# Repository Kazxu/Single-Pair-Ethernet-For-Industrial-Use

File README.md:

# Single Pair Ethernet For Industrial Use

## KICAD
KICAD PCB design files for the LTC4296-1 PSE prototype and LTC9111 PD prototype.

## SCCP 

SCCP_2 uses SPI to communicate with the LTC4296-1 prototype. 

See program print for features. 

SCCP classification between LTC4296-1 and LTC9111 can be performed as well.

## ADIN1110 - Development with STM32Cube IDE.

MCU Firmware : STM32L4xx - https://github.com/STMicroelectronics/STM32CubeL4 

LL DRIVERS : ADIN1110 Support files by Analog Devices.

TCP/IP : LWIP 2.1.2 & Callback API from LWIP. 

Serial Monitor : USART.c & USART.h, huart1.Init.BaudRate = 115200

ADC : INIT in Main.c & stm32l4xx_hal_msp.c

Client-side GUI CONCEPT PROTOTYPE - Python, Added as placeholder for showcase.

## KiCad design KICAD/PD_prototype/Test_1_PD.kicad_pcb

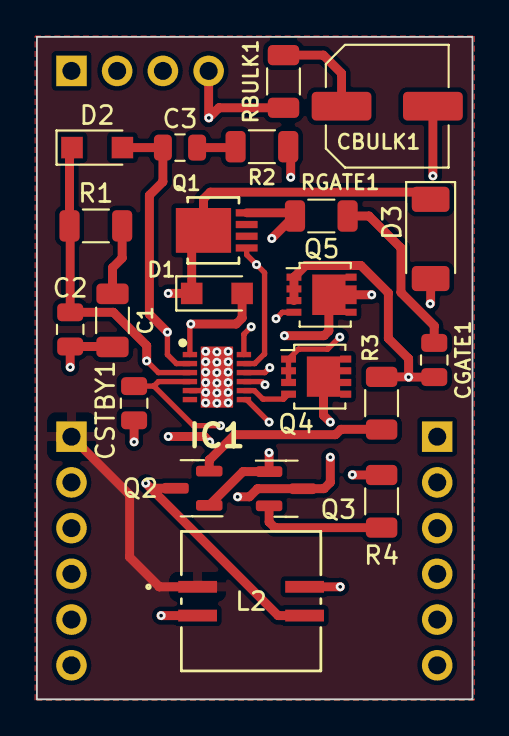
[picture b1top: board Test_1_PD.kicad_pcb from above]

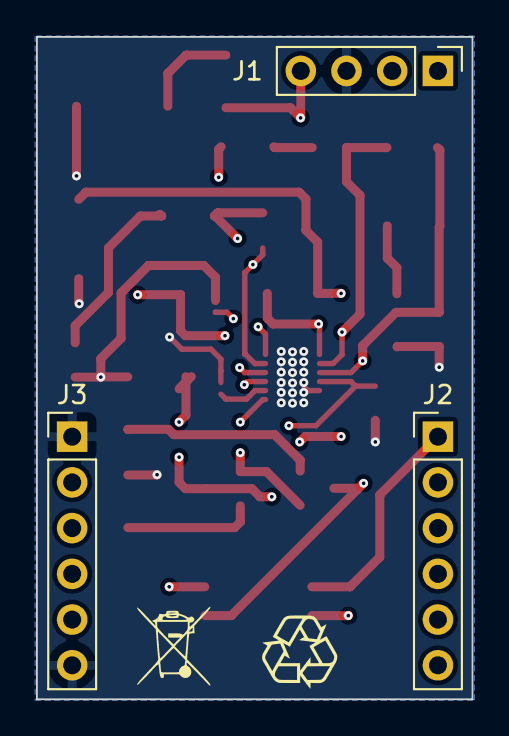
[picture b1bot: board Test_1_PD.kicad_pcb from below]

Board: 4 copper layers, 24.2 x 36.8 mm, 25 parts (3 on the bottom side), 18 nets.

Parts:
C1: 150nF; C_1206_3216Metric
C2, C3: 47nF; C_0805_2012Metric
CBULK1: 47uF; C_Elec_6.3x7.7
CGATE1: 22nF; C_0805_2012Metric
CSTBY1: 2.2uF; C_0805_2012Metric
D1, D2: PMEG10020AELR; Nexperia_CFP3_SOD-123W
D3: D_Zener; D_SOD-128
IC1: LTC9111RDE#PBF; SON50P300X400X80-13N-D
J1: Conn_01x04_Pin; PinHeader_1x04_P2.54mm_Vertical
J2, J3: Conn_01x06_Pin; PinHeader_1x06_P2.54mm_Vertical
L2: MSD7342-683MLC; MSD7342_COC
Q1: PSMN075-100MSEX; LFPAK33_SOT1210_NEX
Q2, Q3: BSS123; SOT-23
Q4, Q5: BUK9M120-100EX; LFPAK33
R1: 40, 1/4; R_1206_3216Metric
R2: 100; R_1206_3216Metric
R3, R4: 3.3, 1/4; R_1206_3216Metric
RBULK1: 3.3, 1/4; R_1206_3216Metric
RGATE1: 10k; R_1206_3216Metric

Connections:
/PODL+: J2.1, L2.1
/PODL-: J2.6, L2.4
GND: C1.2, C2.2, CBULK1.2, CGATE1.2, CSTBY1.2, D3.2 (A), IC1.5 (CLASSV), IC1.13 (GND), J1.3, J3.1, J3.6, Q4.1 (S), Q4.2 (S), Q4.3 (S), Q5.1 (S), Q5.2 (S), Q5.3 (S), R3.2, R4.2
unnamed: C1.1, R1.2
unnamed: C3.1, R2.2
unnamed: CBULK1.1, RBULK1.2
unnamed: CGATE1.1, RGATE1.2
unnamed: D1.2 (A), IC1.1 (SNS1), L2.3, Q2.3 (D), Q5.5 (D), R2.1
unnamed: C2.1, D1.1 (K), D2.1 (K), D3.1 (K), IC1.3 (IN), Q1.5 (D), R1.1
unnamed: C3.2, D2.2 (A), IC1.2 (SNS2), L2.2, Q3.3 (D), Q4.5 (D)
unnamed: CSTBY1.1, IC1.4 (STBY), IC1.10 (CLASSC)
unnamed: IC1.12 (GATE), Q1.4 (G), RGATE1.1
unnamed: IC1.9 (LGATE1), Q5.4 (G)
unnamed: IC1.8 (LGATE2), Q4.4 (G)
unnamed: IC1.11 (OUT), J1.4, Q1.1 (S), RBULK1.1
unnamed: IC1.7 (SCCP), Q2.1 (G), Q3.1 (G)
unnamed: Q2.2 (S), R3.1
unnamed: Q3.2 (S), R4.1

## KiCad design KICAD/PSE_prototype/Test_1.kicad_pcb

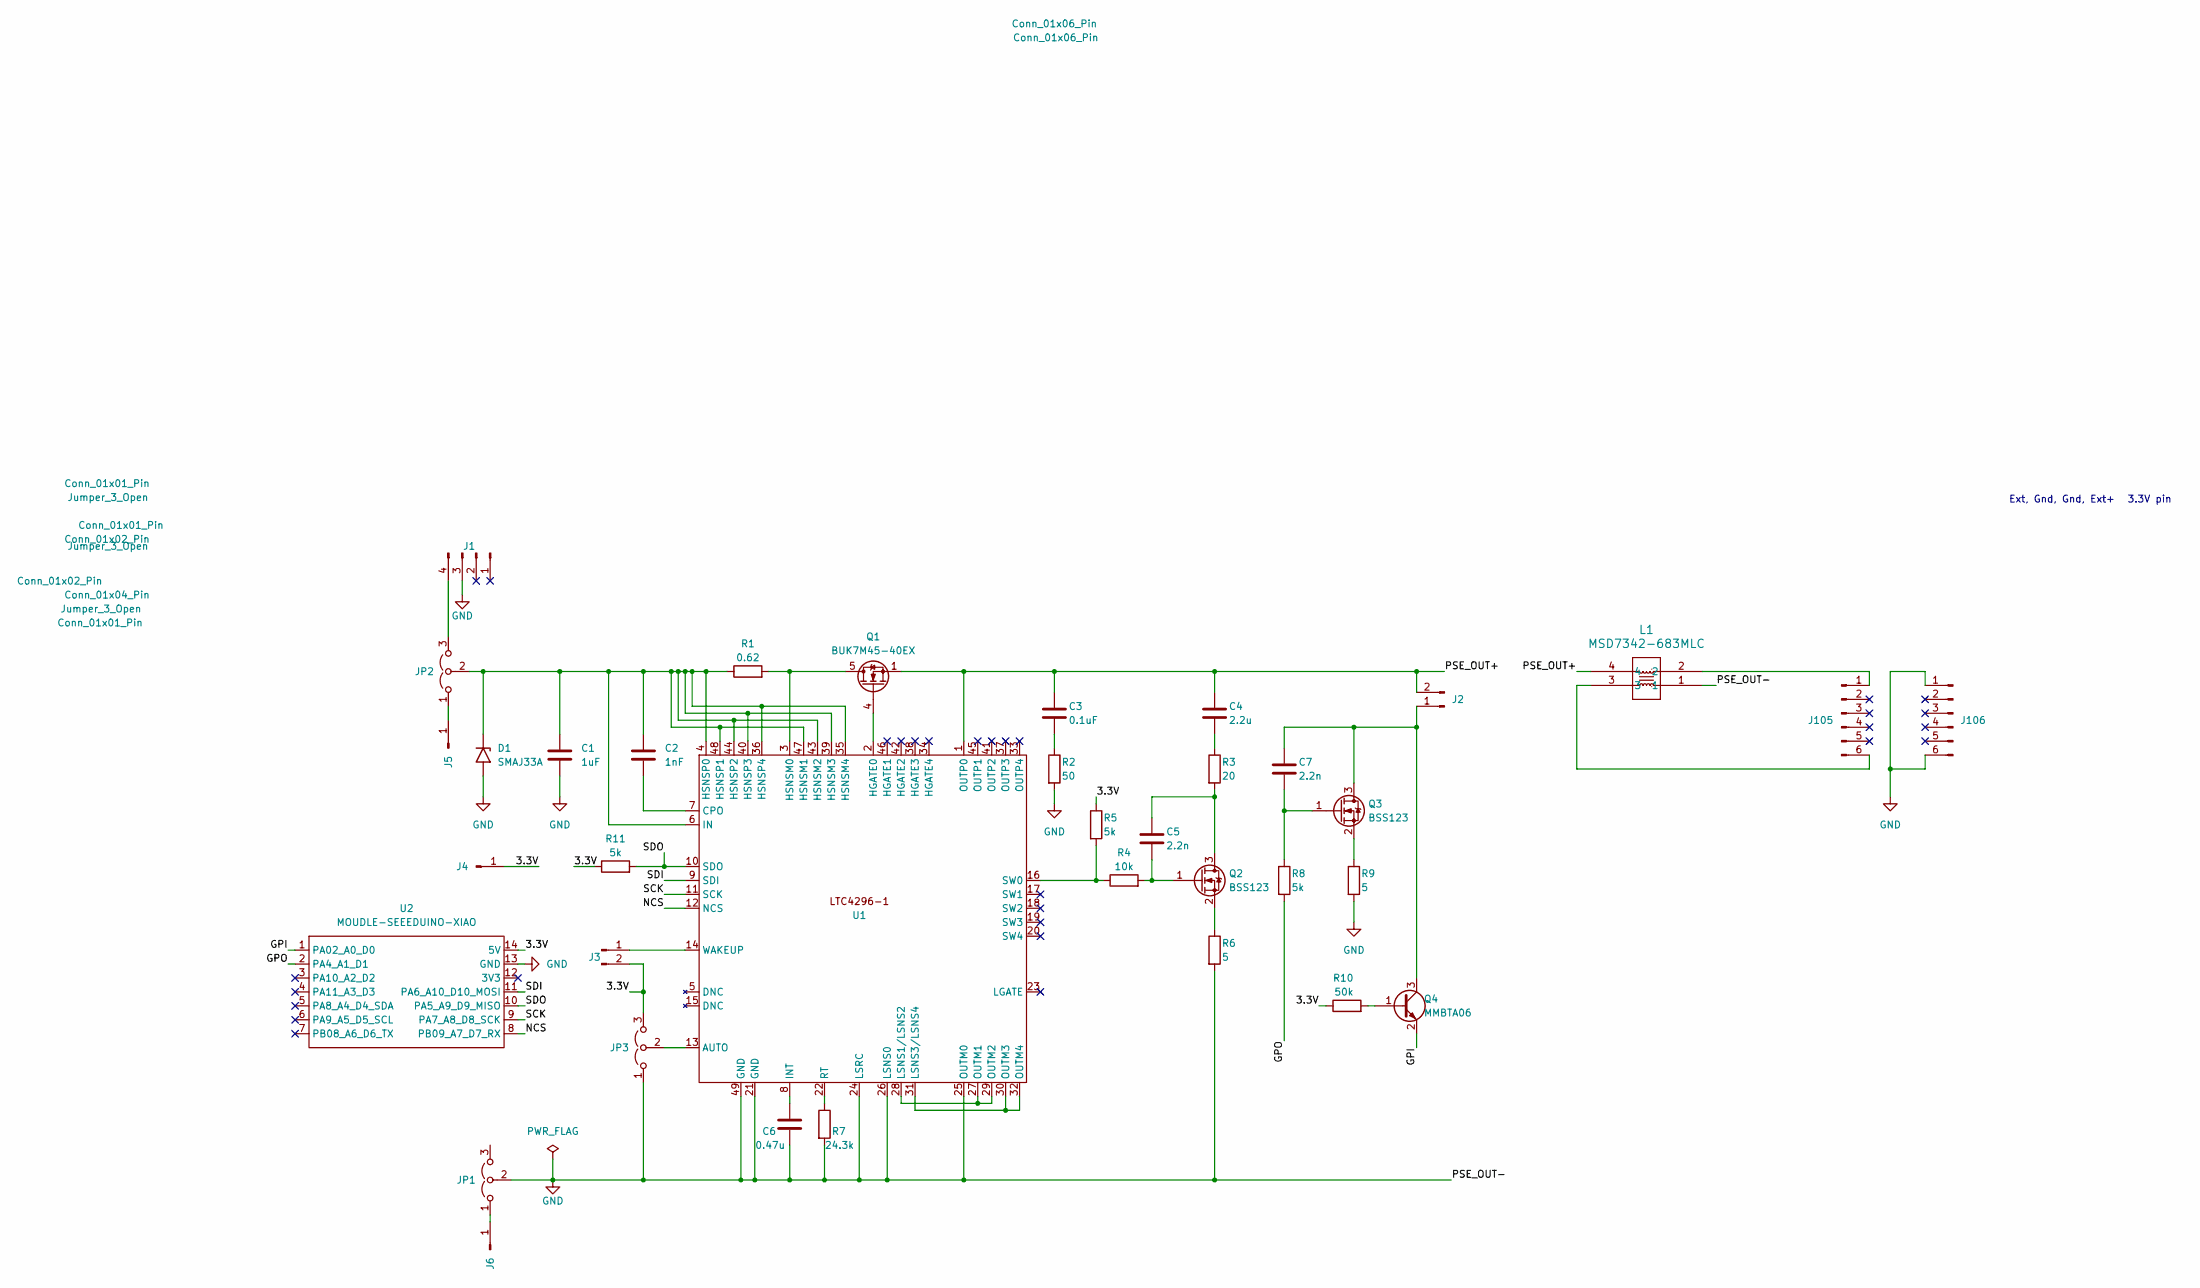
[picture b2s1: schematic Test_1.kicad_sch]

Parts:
C1: 1uF; C_0805_2012Metric
C2: 1nF; C_0805_2012Metric
C3: 0.1uF; C_0805_2012Metric
C4: 2.2u; C_0805_2012Metric
C5, C7: 2.2n; C_0805_2012Metric
C6: 0.47u; C_1206_3216Metric
D1: SMAJ33A; D_SMA
J1: Conn_01x04_Pin; PinHeader_1x04_P2.54mm_Vertical
J2, J3: Conn_01x02_Pin; PinHeader_1x02_P2.54mm_Vertical
J4, J5, J6: Conn_01x01_Pin; PinHeader_1x01_P2.54mm_Vertical
J105, J106: Conn_01x06_Pin; PinHeader_1x06_P2.54mm_Vertical
JP1, JP2, JP3: Jumper_3_Open; PinHeader_1x03_P2.54mm_Vertical
L1: MSD7342-683MLC; MSD7342_COC
Q1: BUK7M45-40EX; LFPAK33
Q2, Q3: BSS123; SOT-23
Q4: MMBTA06; SOT-23
R1: 0.62; R_1206_3216Metric
R2: 50; R_0603_1608Metric
R3: 20; R_0805_2012Metric
R4: 10k; R_0805_2012Metric
R5, R8, R11: 5k; R_0805_2012Metric
R6, R9: 5; R_0805_2012Metric
R7: 24.3k; R_0805_2012Metric
R10: 50k; R_0805_2012Metric
U1: QFN-48-1EP_7x7mm_P0.5mm_EP5.3x5.3mm
U2: MOUDLE-SEEEDUINO-XIAO; MOUDLE14P-2.54-21X17.8MM

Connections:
/3.3V: J3.2, J4.1, JP3.3 (B), R5.1, R10.1, R11.1, U2.14 (5V)
/OUT+: C3.1, C4.1, J2.2, L1.4, Q1.1 (S), Q1.2 (S), Q1.3 (S), U1.1 (OUTP0)
GND: C1.2, C6.2, D1.2 (A2), J1.3, J106.1, J106.6, JP1.2 (C), JP1.3 (B), JP3.1 (A), L1.1, R2.2, R6.2, R7.2, R9.2, U1.21 (GND), U1.24 (LSRC), U1.25 (OUTM0), U1.26 (LSNS0), U1.49 (GND), U2.13 (GND)
unnamed: C3.2, R2.1
unnamed: C4.2, R3.1
unnamed: C1.1, C2.1, D1.1 (A1), JP2.2 (C), R1.1, U1.4 (HSNSP0), U1.6 (IN), U1.35 (HSNSM4), U1.36 (HSNSP4), U1.39 (HSNSM3), U1.40 (HSNSP3), U1.43 (HSNSM2), U1.44 (HSNSP2), U1.47 (HSNSM1), U1.48 (HSNSP1)
unnamed: J1.4, JP2.3 (B)
unnamed: C7.1, J2.1, Q3.3 (D), Q4.3 (C)
unnamed: J3.1, U1.14 (WAKEUP)
unnamed: J5.1, JP2.1 (A)
unnamed: J6.1, JP1.1 (A)
unnamed: J105.1, L1.2
unnamed: J105.6, L1.3
unnamed: JP3.2 (C), U1.13 (AUTO)
unnamed: Q1.5 (D), R1.2, U1.3 (HSNSM0)
unnamed: Q1.4 (G), U1.2 (HGATE0)
unnamed: C5.1, Q2.3 (D), R3.2
unnamed: C5.2, Q2.1 (G), R4.2
unnamed: Q2.2 (S), R6.1
unnamed: C7.2, Q3.1 (G), R8.1
unnamed: Q3.2 (S), R9.1
unnamed: Q4.1 (B), R10.2
unnamed: Q4.2 (E), U2.1 (PA02_A0_D0)
unnamed: C2.2, U1.7 (CPO)
unnamed: C6.1, U1.8 (INT)
unnamed: U1.27 (OUTM1), U1.28 (LSNS1/LSNS2), U1.29 (OUTM2)
unnamed: U1.30 (OUTM3), U1.31 (LSNS3/LSNS4), U1.32 (OUTM4)
unnamed: U1.12 (NCS), U2.8 (PB09_A7_D7_RX)
unnamed: R7.1, U1.22 (RT)
unnamed: U1.11 (SCK), U2.9 (PA7_A8_D8_SCK)
unnamed: U1.9 (SDI), U2.11 (PA6_A10_D10_MOSI)
unnamed: R11.2, U1.10 (SDO), U2.10 (PA5_A9_D9_MISO)
unnamed: R4.1, R5.2, U1.16 (SW0)
unnamed: R8.2, U2.2 (PA4_A1_D1)

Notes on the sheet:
Ext, Gnd, Gnd, Ext+
3.3V pin

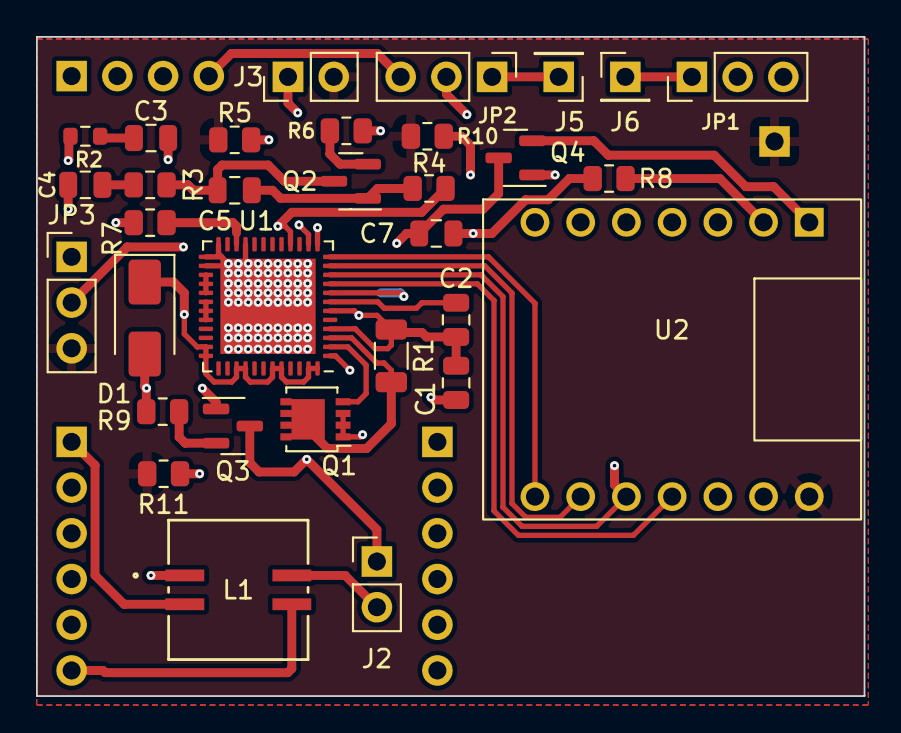
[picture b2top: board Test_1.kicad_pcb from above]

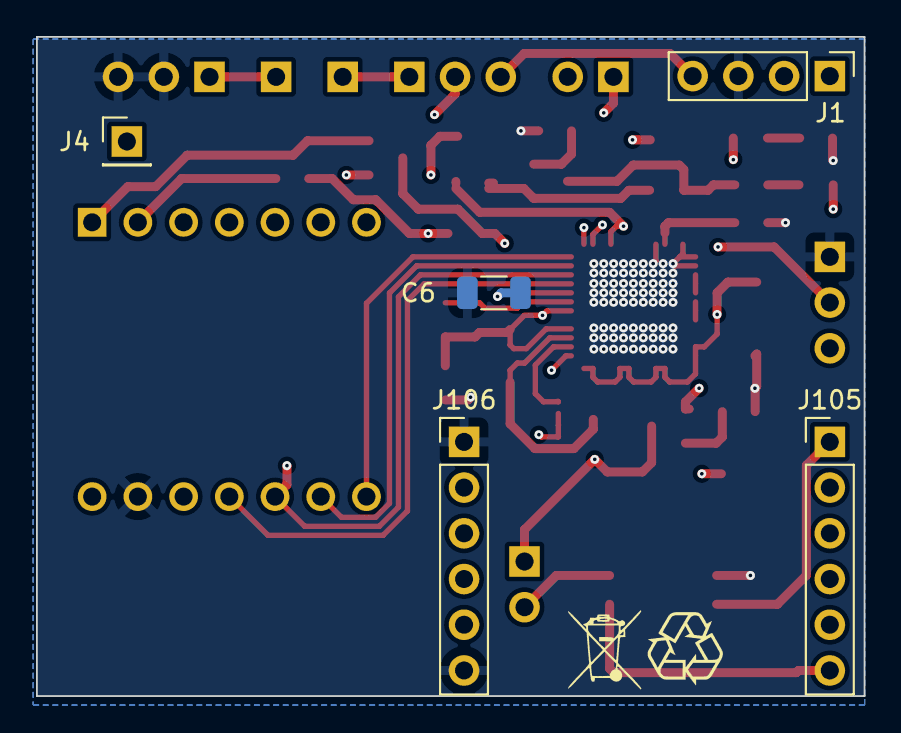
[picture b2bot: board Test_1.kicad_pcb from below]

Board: 4 copper layers, 46.0 x 36.6 mm, 37 parts (5 on the bottom side), 34 nets.

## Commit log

2024-04-24 ADIN TCP FUNKER IKKE, MEN ICMP FUNKER
2024-04-24 TCP SERVER FUNKER, ECHO FUNKER, SEND I WHILE FUNKER IKKE
2024-04-24 Endret README
2024-04-29 Added TCP ECHO hvert 500 MS basert på LWIP TIME OG SYSTICK + comments
2024-05-14 Changed Global to stream data, ADC still no value
2024-05-20 Fixed Buffer to stream data through Serial Monitor, ADC still no value, buffer now shared through Echo server and Main
2024-05-21 JUST ADC WORKS AND SERIAL MONITOR
2024-05-21 Just to keep updated
2024-05-21 Update README.md
    Changed for shared usage
2024-05-21 Added SCCP, changed ADIN1110 Folder.
    Changed README, ADDED SCCP, ADIN1110 has its own folder.
2024-05-21 Update README.md
    Fixed the language.
2024-05-21 Update README.md
    Fixed Spacing in Readme.
2024-05-22 ADDED KICAD + changed README
2024-05-24 ADC Implemented & FIXED, NON-Calibrated
2024-05-27 CONCEPT PROTOTYPE GUI ADDED, TCP sends mA Value
2024-05-28 Update README.md
    Just hiding IP, can change IP through editors.
2024-06-04 Changed Readme, deleted unused file, adjusted comments
2024-06-04 Removed GUI.py, its in the wrong folder
2024-06-05 SCCP - MFVS added
2024-06-05 Update README.md
    More detailed informasjon about ADIN1110
2024-06-06 TCP heartbeat check for CLIENT SIDE PROTOTYPE
2024-06-06 Changed README, ADDED IDE USAGE INFO
